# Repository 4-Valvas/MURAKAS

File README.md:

# MURAKAS
MURAKAS is my first attempt of prototyping a device,  PCB design and logging the processes to make a device network with uses low power and has a long range. 

Name is acronym in Estonian: Maas Ulatuv Raadiosidega vArustatud Keskne Andurite Süsteem

# MURAKAS V1
V1 is the first idea on paper. I used an Arduino pro mini and a LoRa rfm95 to test the concept. Due to LoRa rfm95´s smaller pin header, I decided to also make my first PCB.
V1 proved that this system is possible and works.
Sender a receiver codes are LoRa library example codes.
PCB files of V1 are not available due to lack of skill when design it, and I think that you can make a better design if you want to replicate this system.

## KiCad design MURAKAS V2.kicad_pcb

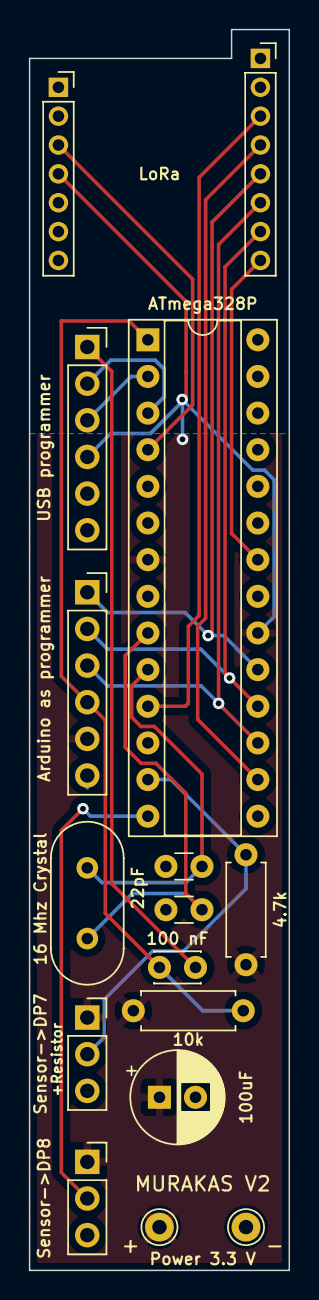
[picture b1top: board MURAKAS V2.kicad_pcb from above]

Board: 2 copper layers, 18.0 x 86.0 mm, 16 parts (0 on the bottom side), 16 nets.

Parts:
C1: 22pF; C_Disc_D3.0mm_W1.6mm_P2.50mm
C2: C; C_Disc_D3.0mm_W1.6mm_P2.50mm
C3: 100 nF; C_Disc_D3.0mm_W2.0mm_P2.50mm
C4: 100uF; CP_Radial_D6.3mm_P2.50mm
J1: Conn_01x07_Female; PinSocket_1x07_P2.00mm_Vertical
J2: USB programmer; PinSocket_1x06_P2.54mm_Vertical
J3: Arduino as programmer; PinSocket_1x06_P2.54mm_Vertical
J4: Sensor->DP8; PinSocket_1x03_P2.54mm_Vertical
J5: Conn_01x08_Male; PinSocket_1x08_P2.00mm_Vertical
J6: Sensor->DP7; PinSocket_1x03_P2.54mm_Vertical
J7, J8: Conn_01x01_Female; Pin_D1.0mm_L10.0mm
R1: 10k; R_Axial_DIN0207_L6.3mm_D2.5mm_P7.62mm_Horizontal
R2: 4.7k; R_Axial_DIN0207_L6.3mm_D2.5mm_P7.62mm_Horizontal
U1: ATmega328P; DIP-28_W7.62mm_Socket
Y1: 16 Mhz Crystal; Crystal_HC18-U_Vertical

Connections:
GND: C1.1, C2.1, C4.2, J2.6, J3.6, J4.3, J5.8, J6.3, J7.1, U1.8 (GND), U1.22 (GND)
unnamed: C1.2, U1.10 (XTAL2/PB7), Y1.2
unnamed: C2.2, U1.9 (XTAL1/PB6), Y1.1
unnamed: C3.1, J3.4, R1.2, U1.1 (~RESET/PC6)
unnamed: C3.2, J2.1
unnamed: J1.3, U1.4 (PD2)
unnamed: J2.2, U1.3 (PD1)
unnamed: J2.3, U1.2 (PD0)
unnamed: J3.1, J5.5, U1.19 (PB5)
unnamed: J3.2, J5.7, U1.18 (PB4)
unnamed: J3.3, J5.6, U1.17 (PB3)
unnamed: J4.2, U1.14 (PB0)
unnamed: J5.3, U1.11 (PD5)
unnamed: J5.4, U1.16 (PB2)
unnamed: J6.2, R2.2, U1.13 (PD7)
VCC: C4.1, J1.4, J2.4, J3.5, J4.1, J6.1, J8.1, R1.1, R2.1, U1.7 (VCC), U1.20 (AVCC)

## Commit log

2023-02-01 MURAKAS Sender code
    Code for sending data over LoRa protocol.
2023-09-12 Update README.md
    fixed readme
